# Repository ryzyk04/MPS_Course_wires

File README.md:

# Головоломка «Провода»

Головоломка сделана на основе Arduino Uno. Игрок разрывает нужные провода по правилам задания. Лента показывает цвет каждого из пяти проводов, отдельный светодиод показывает состояние игры.

## Подключение

| Элемент | Пины Arduino Uno | Подключение |
|---|---|---|
| Провода 1–5 | D3–D7 | Каждый провод замыкает свой вход на GND. Внутренние подтяжки дают LOW при замкнутом проводе и HIGH при разрыве. |
| Лента из пяти WS2812B | D8 | DIN через резистор 330 Ом. По одному пикселю на провод. |
| Индикатор состояния WS2812B | D9 | DIN через отдельный резистор 330 Ом. |
| I²C | A4 (SDA), A5 (SCL) | Линии общей шины. |
| Питание | 5V, GND | Лента и индикатор питаются от 5 В. Земля общая для всех модулей. |

## Текущая прошивка

Код пока рассчитан на стенд: D8 управляет лентой из восьми пикселей, D9 читает кнопку, D10/D11 связывают Uno с ESP32 по UART. Uno опрашивает Simon и «Лабиринт» по I²C. Подключение из таблицы будет использоваться после переноса прошивки.

Параметры игры и обмена находятся в [include/Config.h](include/Config.h). Подключение стенда и протокол описаны в [docs/bus.md](docs/bus.md).

## Сборка и тесты

Из каталога проекта:

```powershell
pio run
python test/run_tests.py
```

Для сборки нужен PlatformIO и соседний каталог `puzzle_bus`. Для тестов нужны Python и `g++`.

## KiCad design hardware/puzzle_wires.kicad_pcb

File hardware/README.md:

# Плата головоломки «Провода»

Плата сделана на основе Arduino Uno. На схеме используется ATmega328P-P в корпусе DIP-28 с кварцем 16 МГц и питанием 5 В. Чтобы открыть схему и трассировку в KiCad, откройте [puzzle_wires.kicad_pro](puzzle_wires.kicad_pro).

## Разъёмы

| Разъём | Назначение | Контакты |
|---|---|---|
| J1 · PWR_5V | Питание платы | 1 — +5 В, 2 — GND |
| J2 · AVR_ISP | Прошивка микроконтроллера | 1 — MISO, 2 — +5 В, 3 — SCK, 4 — MOSI, 5 — RESET, 6 — GND |
| J3–J7 · WIRE_1–WIRE_5 | Пять игровых проводов | Контакт 1 каждого разъёма идёт на вход МК, контакт 2 — на GND |
| J8 · LED_STRIP | Лента из пяти WS2812B, по одному пикселю на провод | 1 — +5 В, 2 — DIN от PB0 (вывод 14) через 330 Ом, 3 — GND |
| J9 · LED_STATUS | Отдельный индикатор состояния WS2812B | 1 — +5 В, 2 — DIN от PB1 (вывод 15) через 330 Ом, 3 — GND |
| J10 · I²C | Общая шина | 1 — SDA, PC4 (вывод 27), 2 — SCL, PC5 (вывод 28). Общая земля подключается через питание. |

Входы J3–J7 по порядку подключены к PD3, PD4, PD5, PD6 и PD7 (выводы 5, 6, 11, 12 и 13). При включённых внутренних подтяжках замкнутый провод даёт LOW, разорванный — HIGH.

Состояние прошивки и команды сборки описаны в [README проекта](../README.md).

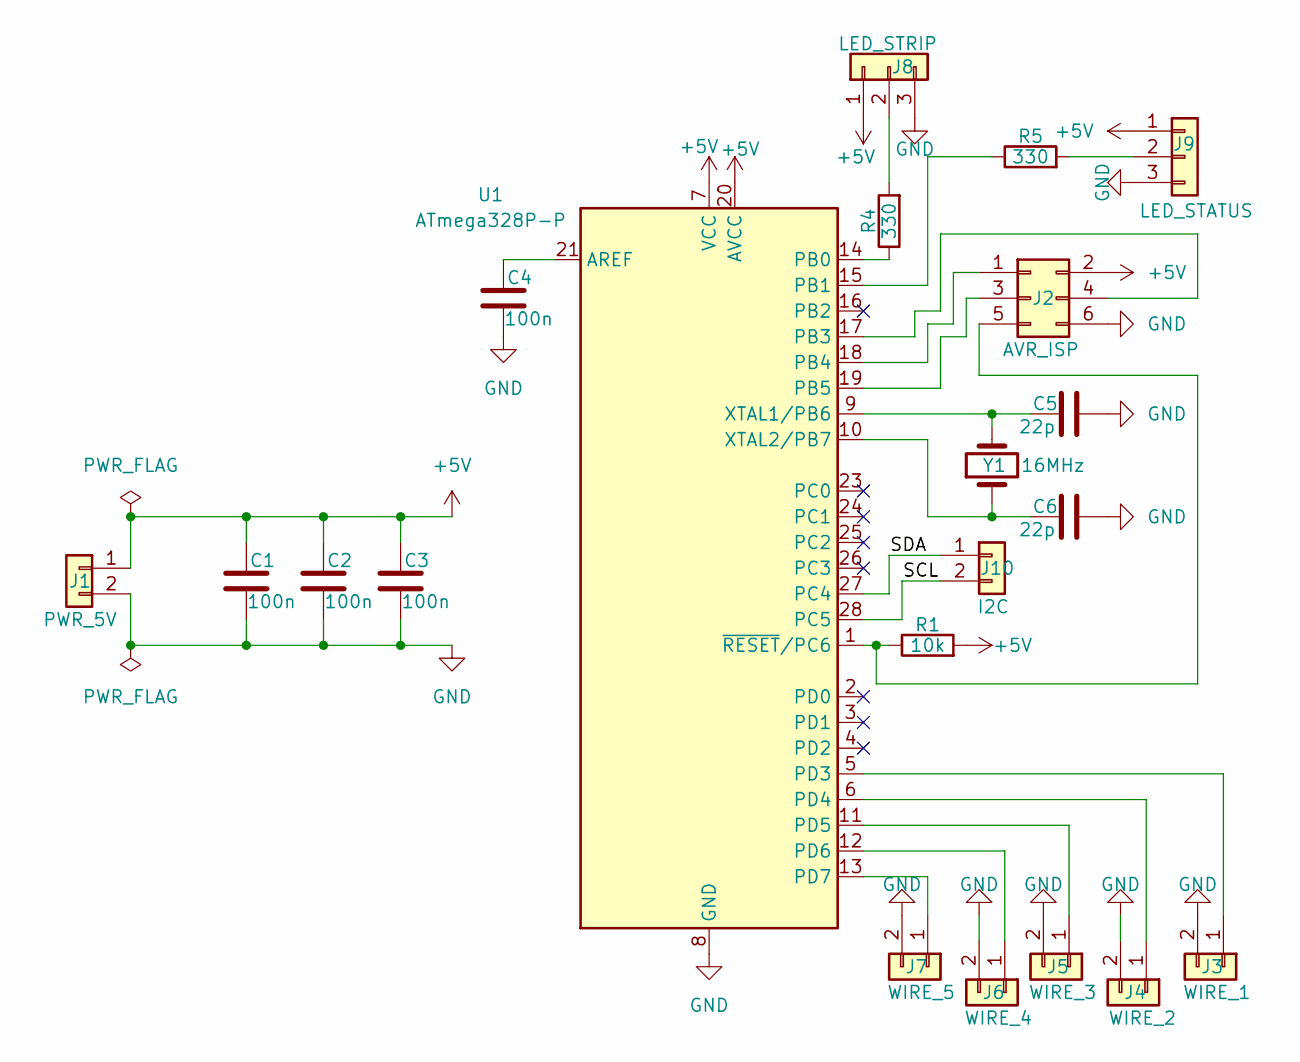
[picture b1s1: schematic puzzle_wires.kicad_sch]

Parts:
C1, C2, C3, C4: 100n; C_0805_2012Metric
C5, C6: 22p; C_0805_2012Metric
J1: PWR_5V; PinHeader_1x02_P2.54mm_Vertical
J2: AVR_ISP; PinHeader_2x03_P2.54mm_Vertical
J3: WIRE_1; PinHeader_1x02_P2.54mm_Vertical
J4: WIRE_2; PinHeader_1x02_P2.54mm_Vertical
J5: WIRE_3; PinHeader_1x02_P2.54mm_Vertical
J6: WIRE_4; PinHeader_1x02_P2.54mm_Vertical
J7: WIRE_5; PinHeader_1x02_P2.54mm_Vertical
J8: LED_STRIP; PinHeader_1x03_P2.54mm_Vertical
J9: LED_STATUS; PinHeader_1x03_P2.54mm_Vertical
J10: I2C; PinHeader_1x02_P2.54mm_Vertical
R1: 10k; R_0805_2012Metric
R4, R5: 330; R_0805_2012Metric
U1: ATmega328P-P; DIP-28_W7.62mm
Y1: 16MHz; Crystal_HC49-4H_Vertical

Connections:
+5V: C1.2, C2.2, C3.2, J1.1, J2.2, J8.1, J9.1, R1.2, U1.7 (VCC), U1.20 (AVCC)
/SCL: J10.2, U1.28 (PC5)
/SDA: J10.1, U1.27 (PC4)
GND: C1.1, C2.1, C3.1, C4.1, C5.1, C6.1, J1.2, J2.6, J3.2, J4.2, J5.2, J6.2, J7.2, J8.3, J9.3, U1.8 (GND), U1.22 (GND)
unnamed: J2.1, U1.18 (PB4)
unnamed: J2.3, U1.19 (PB5)
unnamed: J2.4, U1.17 (PB3)
unnamed: J2.5, R1.1, U1.1 (~RESET/PC6)
unnamed: J3.1, U1.5 (PD3)
unnamed: J4.1, U1.6 (PD4)
unnamed: J5.1, U1.11 (PD5)
unnamed: J6.1, U1.12 (PD6)
unnamed: J7.1, U1.13 (PD7)
unnamed: J8.2, R4.2
unnamed: J9.2, R5.2
unnamed: C4.2, U1.21 (AREF)
unnamed: R4.1, U1.14 (PB0)
unnamed: R5.1, U1.15 (PB1)
unnamed: C5.2, U1.9 (XTAL1/PB6), Y1.2
unnamed: C6.2, U1.10 (XTAL2/PB7), Y1.1

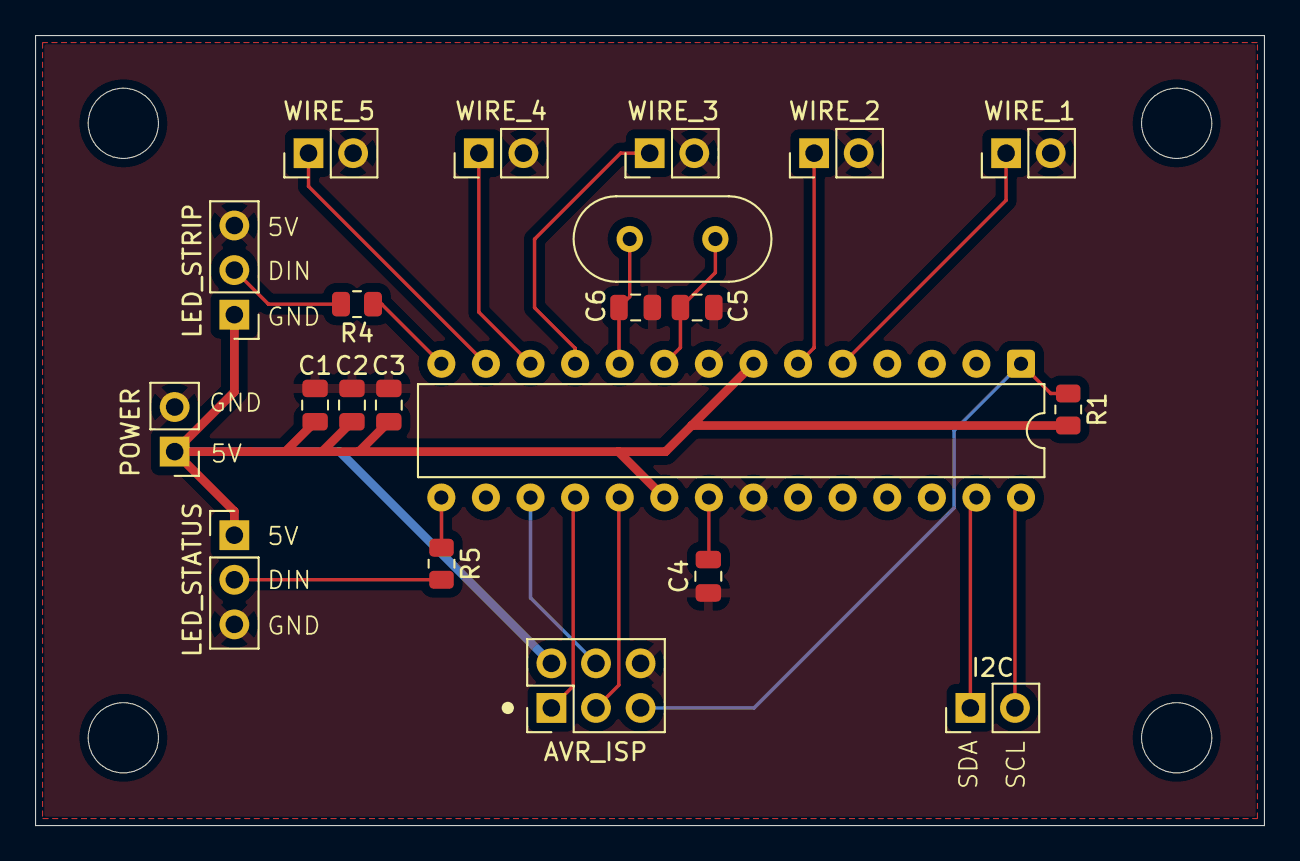
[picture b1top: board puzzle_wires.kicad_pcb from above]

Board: 2 copper layers, 70.0 x 45.0 mm, 21 parts (0 on the bottom side), 20 nets.
